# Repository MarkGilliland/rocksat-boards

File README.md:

# rocksat-boards
Mines RockSat-X Circuit Boards. Eagle projects, boards, schematics, and libraries

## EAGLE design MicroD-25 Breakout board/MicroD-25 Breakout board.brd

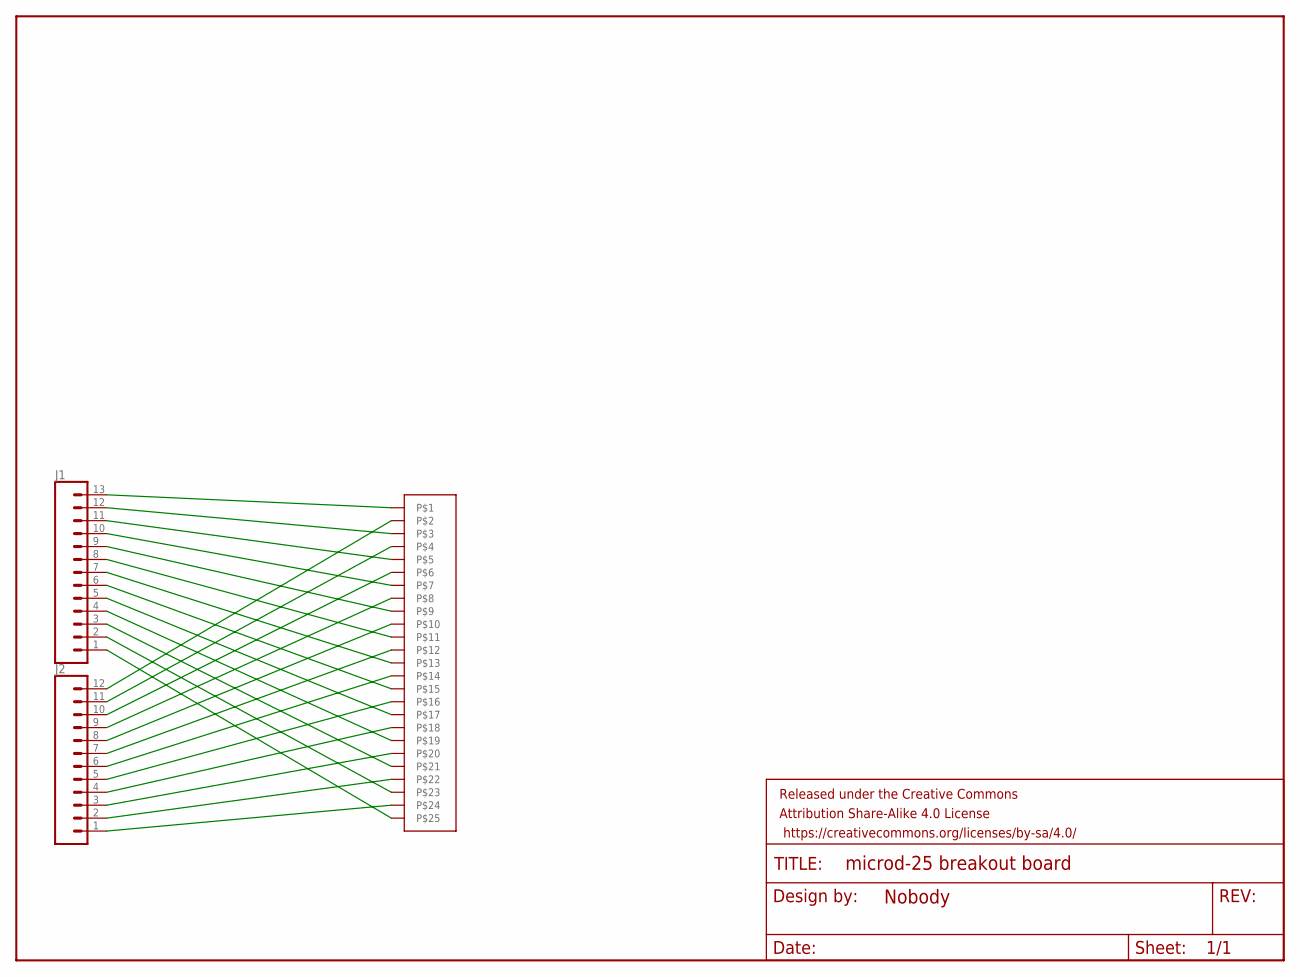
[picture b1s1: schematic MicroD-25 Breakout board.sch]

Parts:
FRAME1: FRAME-LETTERNO_PACKAGE; DUMMY
J1: CONN_13LONGPADS; 1X13-LONGPADS
J2: CONN_12LONGPADS; 1X12_LONGPADS
U$1: MICROD25_FM_RCPT

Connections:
unnamed: J1.13, U$1.PIN1
unnamed: J1.12, U$1.PIN3
unnamed: J1.11, U$1.PIN5
unnamed: J1.10, U$1.PIN7
unnamed: J1.9, U$1.PIN9
unnamed: J1.8, U$1.PIN11
unnamed: J1.7, U$1.PIN13
unnamed: J1.6, U$1.PIN15
unnamed: J1.5, U$1.PIN17
unnamed: J1.4, U$1.PIN19
unnamed: J1.3, U$1.PIN21
unnamed: J1.2, U$1.PIN23
unnamed: J1.1, U$1.PIN25
unnamed: J2.12, U$1.PIN2
unnamed: J2.11, U$1.PIN4
unnamed: J2.10, U$1.PIN6
unnamed: J2.9, U$1.PIN8
unnamed: J2.8, U$1.PIN10
unnamed: J2.7, U$1.PIN12
unnamed: J2.6, U$1.PIN14
unnamed: J2.5, U$1.PIN16
unnamed: J2.4, U$1.PIN18
unnamed: J2.3, U$1.PIN20
unnamed: J2.2, U$1.PIN22
unnamed: J2.1, U$1.PIN24

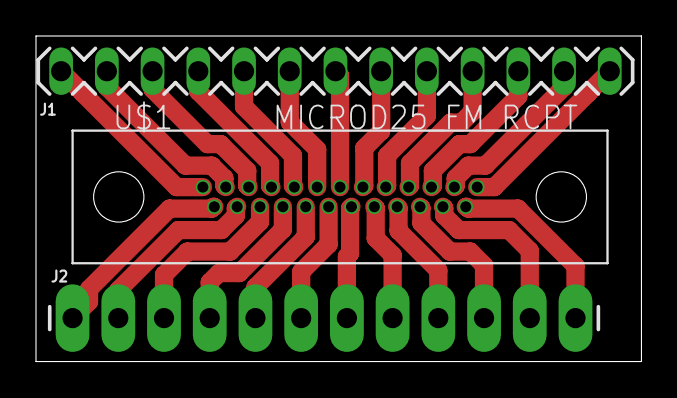
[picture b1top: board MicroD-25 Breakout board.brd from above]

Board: 2 copper layers, 33.6 x 18.1 mm, 4 parts (0 on the bottom side), 25 nets.

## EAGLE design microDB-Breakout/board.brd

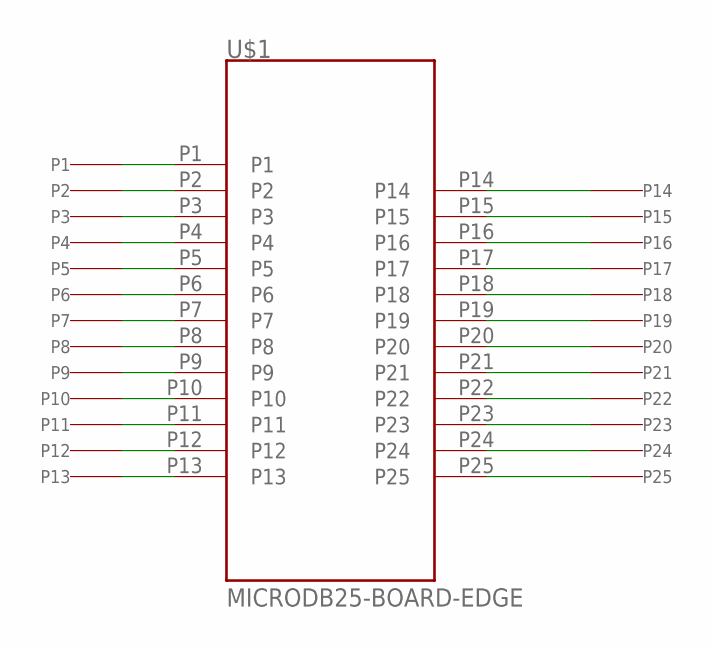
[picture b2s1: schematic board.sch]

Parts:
P1, P2, P3, P4, P5, P6, P7, P8, P9, P10, P11, P12, P13, P14, P15, P16, P17, P18, P19, P20, P21, P22, P23, P24, P25: TP-19MIL
U$1: MICRODB25-BOARD-EDGE

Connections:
unnamed: P1.P1, U$1.P1
unnamed: P2.P1, U$1.P2
unnamed: P3.P1, U$1.P3
unnamed: P4.P1, U$1.P4
unnamed: P5.P1, U$1.P5
unnamed: P6.P1, U$1.P6
unnamed: P7.P1, U$1.P7
unnamed: P8.P1, U$1.P8
unnamed: P9.P1, U$1.P9
unnamed: P10.P1, U$1.P10
unnamed: P11.P1, U$1.P11
unnamed: P12.P1, U$1.P12
unnamed: P13.P1, U$1.P13
unnamed: P14.P1, U$1.P14
unnamed: P15.P1, U$1.P15
unnamed: P16.P1, U$1.P16
unnamed: P17.P1, U$1.P17
unnamed: P18.P1, U$1.P18
unnamed: P19.P1, U$1.P19
unnamed: P20.P1, U$1.P20
unnamed: P21.P1, U$1.P21
unnamed: P22.P1, U$1.P22
unnamed: P23.P1, U$1.P23
unnamed: P24.P1, U$1.P24
unnamed: P25.P1, U$1.P25

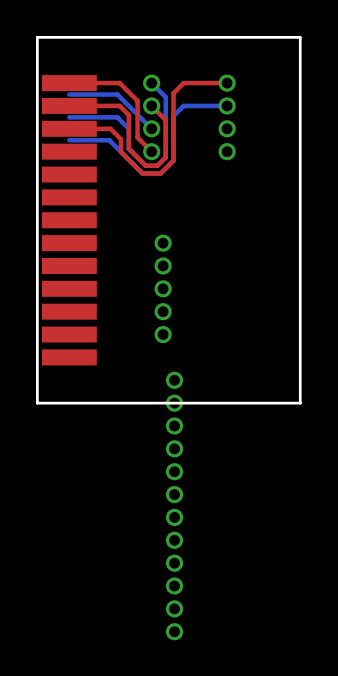
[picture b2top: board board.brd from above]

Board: 2 copper layers, 14.6 x 20.3 mm, 26 parts (0 on the bottom side), 25 nets.

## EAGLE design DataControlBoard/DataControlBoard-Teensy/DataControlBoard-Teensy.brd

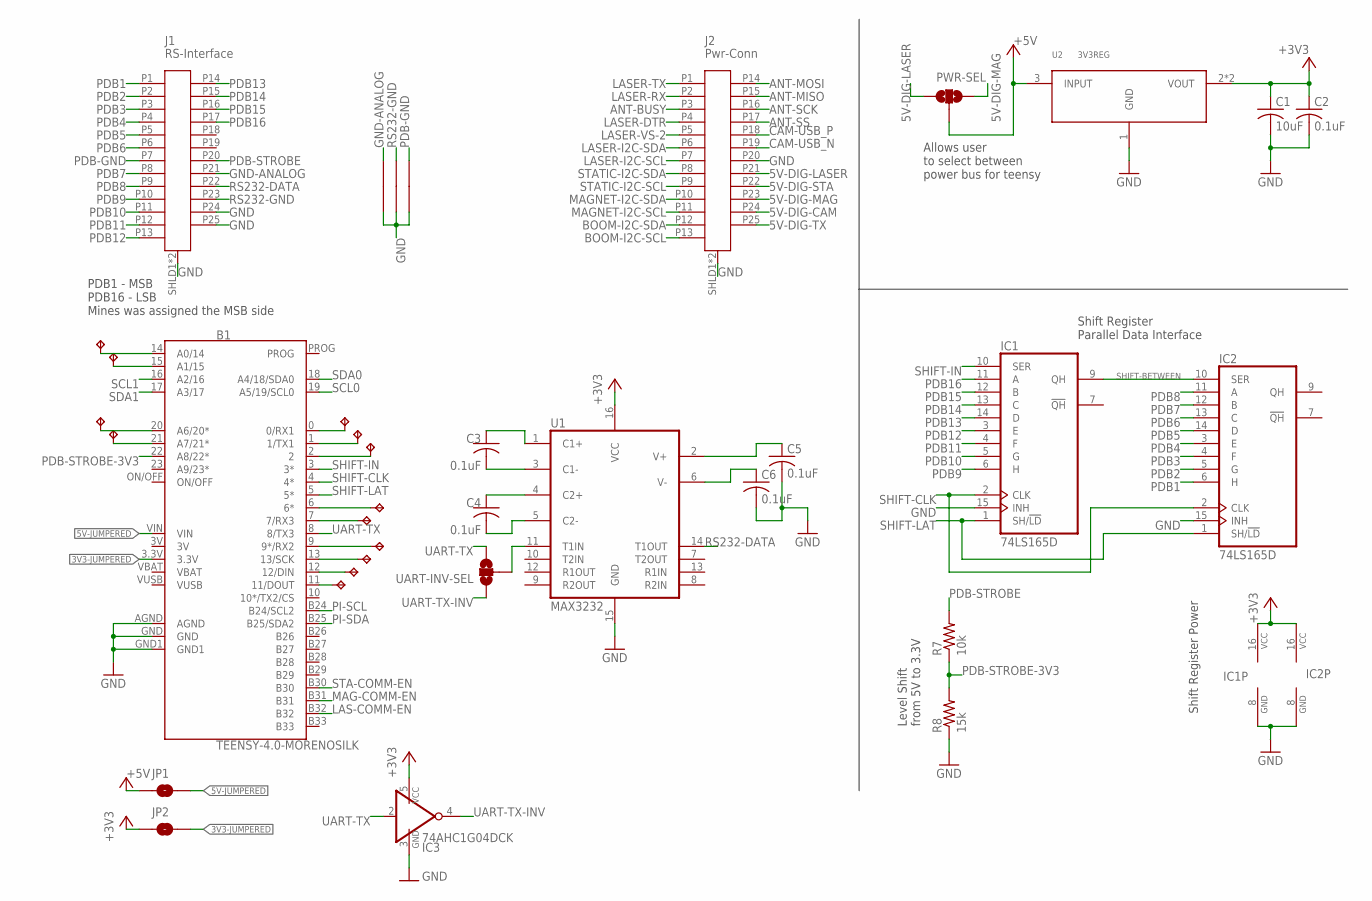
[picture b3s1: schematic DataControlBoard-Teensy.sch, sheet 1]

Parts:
B1: TEENSY-4.0-MORENOSILK; TEENSY-4.0_NOSILK
C1: 10uF; C0805
C2, C3, C4, C5, C6: 0.1uF; C0805
IC1, IC2: 74LS165D; SO16
IC3: 74AHC1G04DCK; SC70-5
J1: RS-Interface; MICRO-D25-RA
J2: Pwr-Conn; MICRO-D25-RA
JP1, JP2: JUMPER-SMT_2_NO_NO-SILK; SMT-JUMPER_2_NO_NO-SILK
PWR-SEL: JUMPER-SMT_3_NO_NO-SILK; SMT-JUMPER_3_NO_NO-SILK
R7: 10k; R0805
R8: 15k; R0805
TP8, TP9, TP10, TP11, TP12, TP13, TP14, TP15, TP16, TP17, TP18, TP19, TP20: TPPAD1-13; P1-13
U1: MAX3232; SO16
U2: 3V3REG; SOT223
U$1, U$2, U$3: GND-MERGER
UART-INV-SEL: JUMPER-SMT_3_NO_NO-SILK; SMT-JUMPER_3_NO_NO-SILK

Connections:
3V: B1.3V
3V3-JUMPERED: B1.3.3V, JP2.2
5V-DIG-CAM: J2.P24; also elsewhere on the board
5V-DIG-LASER: J2.P21, PWR-SEL.1; also elsewhere on the board
5V-DIG-MAG: J2.P23, PWR-SEL.3; also elsewhere on the board
5V-DIG-STA: J2.P22; also elsewhere on the board
5V-DIG-TX: J2.P25; also elsewhere on the board
5V-JUMPERED: B1.VIN, JP1.2
+3V3: C1.1, C2.1, IC1.16 (VCC), IC2.16 (VCC), IC3.5 (VCC), JP2.1, U1.16 (VCC), U2.2 (VOUT), U2.4 (VOUT); also elsewhere on the board
+5V: JP1.1, PWR-SEL.2, U2.3 (INPUT); also elsewhere on the board
ANT-BUSY: J2.P3; also elsewhere on the board
ANT-MISO: J2.P15; also elsewhere on the board
ANT-MOSI: J2.P14; also elsewhere on the board
ANT-SCK: J2.P16; also elsewhere on the board
ANT-SS: J2.P17; also elsewhere on the board
BOOM-I2C-SCL: J2.P13; also elsewhere on the board
BOOM-I2C-SDA: J2.P12; also elsewhere on the board
CAM-USB_N: J2.P19; also elsewhere on the board
CAM-USB_P: J2.P18; also elsewhere on the board
GND: B1.AGND, B1.GND, B1.GND1, C1.2, C2.2, C5.2, C6.2, IC1.8 (GND), IC1.15 (INH), IC2.8 (GND), IC2.15 (INH), IC3.3 (GND), J1.P24, J1.P25, J1.SHLD1 (SHLD), J1.SHLD2 (SHLD), J2.P20, J2.SHLD1 (SHLD), J2.SHLD2 (SHLD), R8.1, U1.15 (GND), U2.1 (GND), U$1.P$1, U$2.P$1, U$3.P$1; also elsewhere on the board
GND-ANALOG: J1.P21, U$1.P$2
LAS-COMM-EN: B1.B32; also elsewhere on the board
LASER-DTR: J2.P4; also elsewhere on the board
LASER-I2C-SCL: J2.P7; also elsewhere on the board
LASER-I2C-SDA: J2.P6; also elsewhere on the board
LASER-RX: J2.P2; also elsewhere on the board
LASER-TX: J2.P1; also elsewhere on the board
LASER-VS-2: J2.P5; also elsewhere on the board
MAG-COMM-EN: B1.B31; also elsewhere on the board
MAGNET-I2C-SCL: J2.P11; also elsewhere on the board
MAGNET-I2C-SDA: J2.P10; also elsewhere on the board
unnamed: B1.0 (0/RX1), TP12.TP
unnamed: B1.1 (1/TX1), TP13.TP
unnamed: B1.2, TP14.TP
unnamed: B1.9 (9*/RX2), TP15.TP
unnamed: B1.13 (13/SCK), TP16.TP
unnamed: B1.12 (12/DIN), TP17.TP
unnamed: B1.11 (11/DOUT), TP18.TP
unnamed: B1.14 (A0/14), TP8.TP
unnamed: B1.15 (A1/15), TP9.TP
unnamed: B1.20 (A6/20*), TP10.TP
unnamed: B1.21 (A7/21*), TP11.TP
unnamed: B1.6 (6*), TP19.TP
unnamed: B1.7 (7/RX3), TP20.TP
unnamed: U1.11 (T1IN), UART-INV-SEL.2
unnamed: C5.1, U1.2 (V+)
unnamed: C6.1, U1.6 (V-)
unnamed: C3.1, U1.1 (C1+)
unnamed: C3.2, U1.3 (C1-)
unnamed: C4.1, U1.4 (C2+)
unnamed: C4.2, U1.5 (C2-)
PDB1: IC2.6 (H), J1.P1
PDB2: IC2.5 (G), J1.P2
PDB3: IC2.4 (F), J1.P3
PDB4: IC2.3 (E), J1.P4
PDB5: IC2.14 (D), J1.P5
PDB6: IC2.13 (C), J1.P6
PDB7: IC2.12 (B), J1.P8
PDB8: IC2.11 (A), J1.P9
PDB9: IC1.6 (H), J1.P10
PDB10: IC1.5 (G), J1.P11
PDB11: IC1.4 (F), J1.P12
PDB12: IC1.3 (E), J1.P13
PDB13: IC1.14 (D), J1.P14
PDB14: IC1.13 (C), J1.P15
PDB15: IC1.12 (B), J1.P16
PDB16: IC1.11 (A), J1.P17
PDB-GND: J1.P7, U$3.P$2
PDB-STROBE: J1.P20, R7.2; also elsewhere on the board
PDB-STROBE-3V3: B1.22 (A8/22*), R7.1, R8.2
PI-SCL: B1.B24 (B24/SCL2); also elsewhere on the board
PI-SDA: B1.B25 (B25/SDA2); also elsewhere on the board
RS232-DATA: J1.P22, U1.14 (T1OUT)
RS232-GND: J1.P23, U$2.P$2
SCL0: B1.19 (A5/19/SCL0); also elsewhere on the board
SCL1: B1.16 (A2/16); also elsewhere on the board
SDA0: B1.18 (A4/18/SDA0); also elsewhere on the board
SDA1: B1.17 (A3/17); also elsewhere on the board
SHIFT-BETWEEN: IC1.9 (QH), IC2.10 (SER)
SHIFT-CLK: B1.4 (4*), IC1.2 (CLK), IC2.2 (CLK)
SHIFT-IN: B1.3 (3*), IC1.10 (SER)
SHIFT-LAT: B1.5 (5*), IC1.1 (SH/!LD), IC2.1 (SH/!LD)
STA-COMM-EN: B1.B30; also elsewhere on the board
STATIC-I2C-SCL: J2.P9; also elsewhere on the board
STATIC-I2C-SDA: J2.P8; also elsewhere on the board
UART-TX: B1.8 (8/TX3), IC3.2 (I), UART-INV-SEL.3
UART-TX-INV: IC3.4 (O), UART-INV-SEL.1
VBAT: B1.VBAT
VUSB: B1.VUSB

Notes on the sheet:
Shift Register Power
Shift Register Parallel Data Interface
Allows user to select between power bus for teensy
Level Shift from 5V to 3.3V
PDB1 - MSB PDB16 - LSB Mines was assigned the MSB side

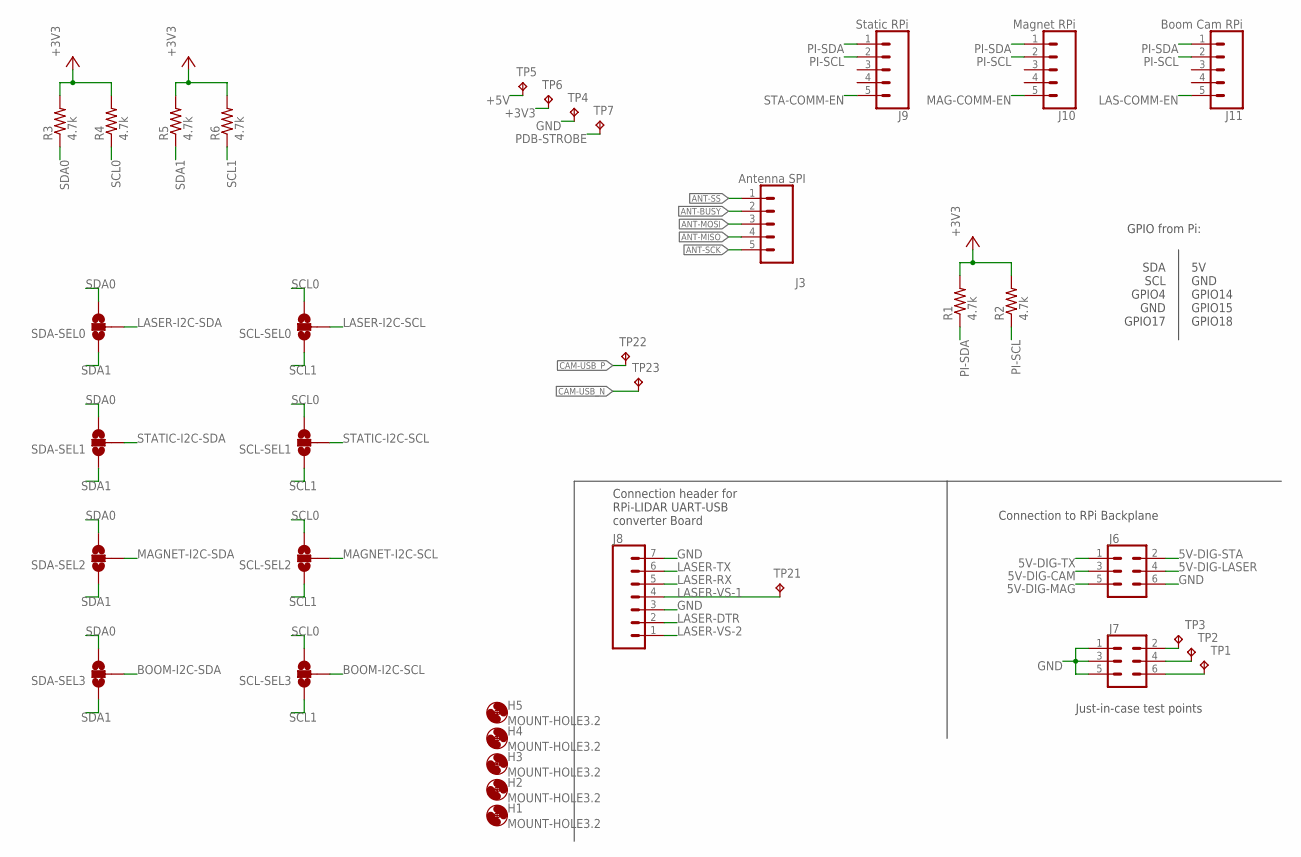
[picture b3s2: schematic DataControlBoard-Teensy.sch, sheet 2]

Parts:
H1, H2, H3, H4, H5: MOUNT-HOLE3.2; 3,2
J3: Antenna SPI; 1X05_LOCK
J6, J7: CONN_03X22X3_SILK_MALE_PTH; 2X3
J8: CONN_07; 1X07
J9: Static RPi; 1X05_LOCK
J10: Magnet RPi; 1X05_LOCK
J11: Boom Cam RPi; 1X05_LOCK
R1, R2, R3, R4, R5, R6: 4.7k; R0805
SCL-SEL0, SCL-SEL1, SCL-SEL2, SCL-SEL3: JUMPER-SMT_3_NO_NO-SILK; SMT-JUMPER_3_NO_NO-SILK
SDA-SEL0, SDA-SEL1, SDA-SEL2, SDA-SEL3: JUMPER-SMT_3_NO_NO-SILK; SMT-JUMPER_3_NO_NO-SILK
TP1, TP2, TP3, TP21, TP22, TP23: TPPAD1-13; P1-13
TP4: GND; P1-13
TP5: 5V; P1-13
TP6: 3.3V; P1-13
TP7: STROBE; P1-13

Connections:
5V-DIG-CAM: J6.3; also elsewhere on the board
5V-DIG-LASER: J6.4; also elsewhere on the board
5V-DIG-MAG: J6.5; also elsewhere on the board
5V-DIG-STA: J6.2; also elsewhere on the board
5V-DIG-TX: J6.1; also elsewhere on the board
+3V3: R1.2, R2.2, R3.2, R4.2, R5.2, R6.2, TP6.TP; also elsewhere on the board
+5V: TP5.TP; also elsewhere on the board
ANT-BUSY: J3.2; also elsewhere on the board
ANT-MISO: J3.4; also elsewhere on the board
ANT-MOSI: J3.3; also elsewhere on the board
ANT-SCK: J3.5; also elsewhere on the board
ANT-SS: J3.1; also elsewhere on the board
BOOM-I2C-SCL: SCL-SEL3.2; also elsewhere on the board
BOOM-I2C-SDA: SDA-SEL3.2; also elsewhere on the board
CAM-USB_N: TP23.TP; also elsewhere on the board
CAM-USB_P: TP22.TP; also elsewhere on the board
GND: J6.6, J7.1, J7.3, J7.5, J8.3, J8.7, TP4.TP; also elsewhere on the board
LAS-COMM-EN: J11.5; also elsewhere on the board
LASER-DTR: J8.2; also elsewhere on the board
LASER-I2C-SCL: SCL-SEL0.2; also elsewhere on the board
LASER-I2C-SDA: SDA-SEL0.2; also elsewhere on the board
LASER-RX: J8.5; also elsewhere on the board
LASER-TX: J8.6; also elsewhere on the board
LASER-VS-1: J8.4, TP21.TP
LASER-VS-2: J8.1; also elsewhere on the board
MAG-COMM-EN: J10.5; also elsewhere on the board
MAGNET-I2C-SCL: SCL-SEL2.2; also elsewhere on the board
MAGNET-I2C-SDA: SDA-SEL2.2; also elsewhere on the board
unnamed: J7.2, TP3.TP
unnamed: J7.4, TP2.TP
unnamed: J7.6, TP1.TP
PDB-STROBE: TP7.TP; also elsewhere on the board
PI-SCL: J9.2, J10.2, J11.2, R2.1; also elsewhere on the board
PI-SDA: J9.1, J10.1, J11.1, R1.1; also elsewhere on the board
SCL0: R4.1, SCL-SEL0.3, SCL-SEL1.3, SCL-SEL2.3, SCL-SEL3.3; also elsewhere on the board
SCL1: R6.1, SCL-SEL0.1, SCL-SEL1.1, SCL-SEL2.1, SCL-SEL3.1; also elsewhere on the board
SDA0: R3.1, SDA-SEL0.3, SDA-SEL1.3, SDA-SEL2.3, SDA-SEL3.3; also elsewhere on the board
SDA1: R5.1, SDA-SEL0.1, SDA-SEL1.1, SDA-SEL2.1, SDA-SEL3.1; also elsewhere on the board
STA-COMM-EN: J9.5; also elsewhere on the board
STATIC-I2C-SCL: SCL-SEL1.2; also elsewhere on the board
STATIC-I2C-SDA: SDA-SEL1.2; also elsewhere on the board

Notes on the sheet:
SDA SCL GPIO4 GND GPIO17
5V GND GPIO14 GPIO15 GPIO18
GPIO from Pi:
Just-in-case test points
Connection to RPi Backplane
Connection header for RPi-LIDAR UART-USB converter Board

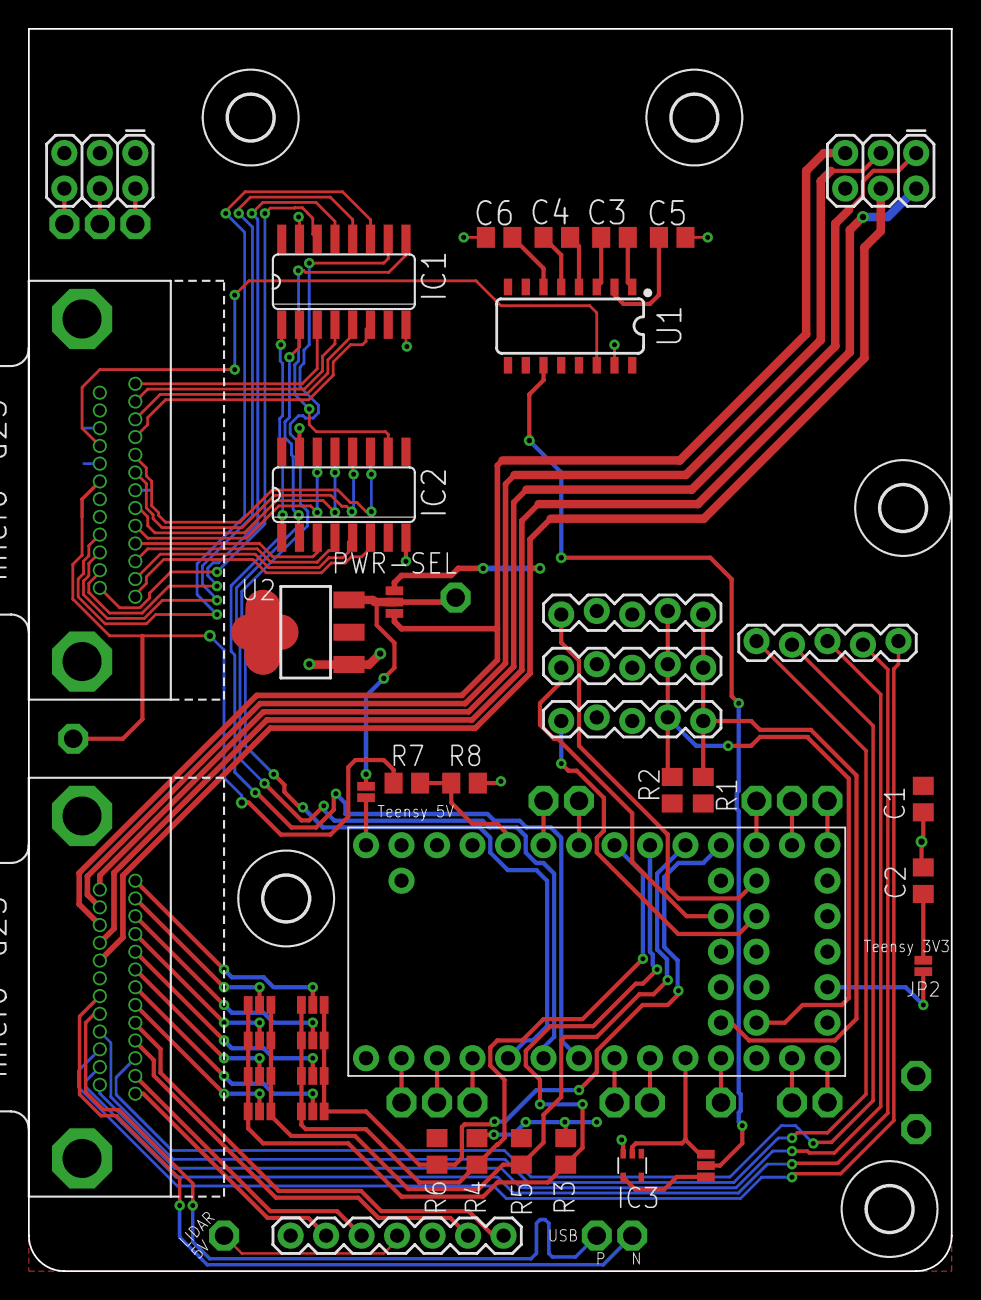
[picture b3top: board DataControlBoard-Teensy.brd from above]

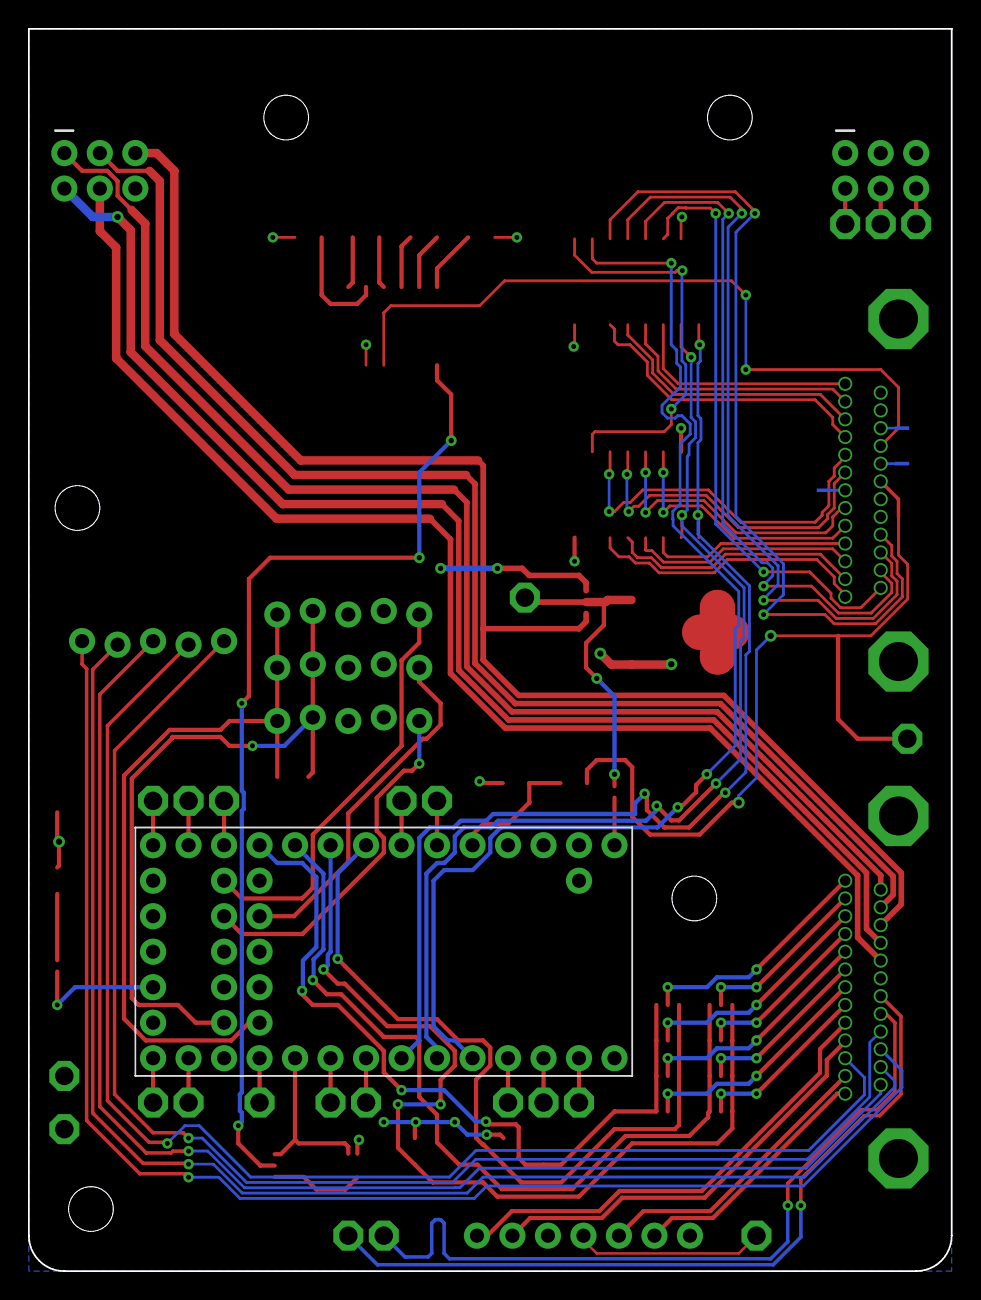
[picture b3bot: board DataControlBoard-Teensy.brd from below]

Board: 2 copper layers, 66.0 x 88.9 mm, 72 parts (3 on the bottom side), 90 nets.

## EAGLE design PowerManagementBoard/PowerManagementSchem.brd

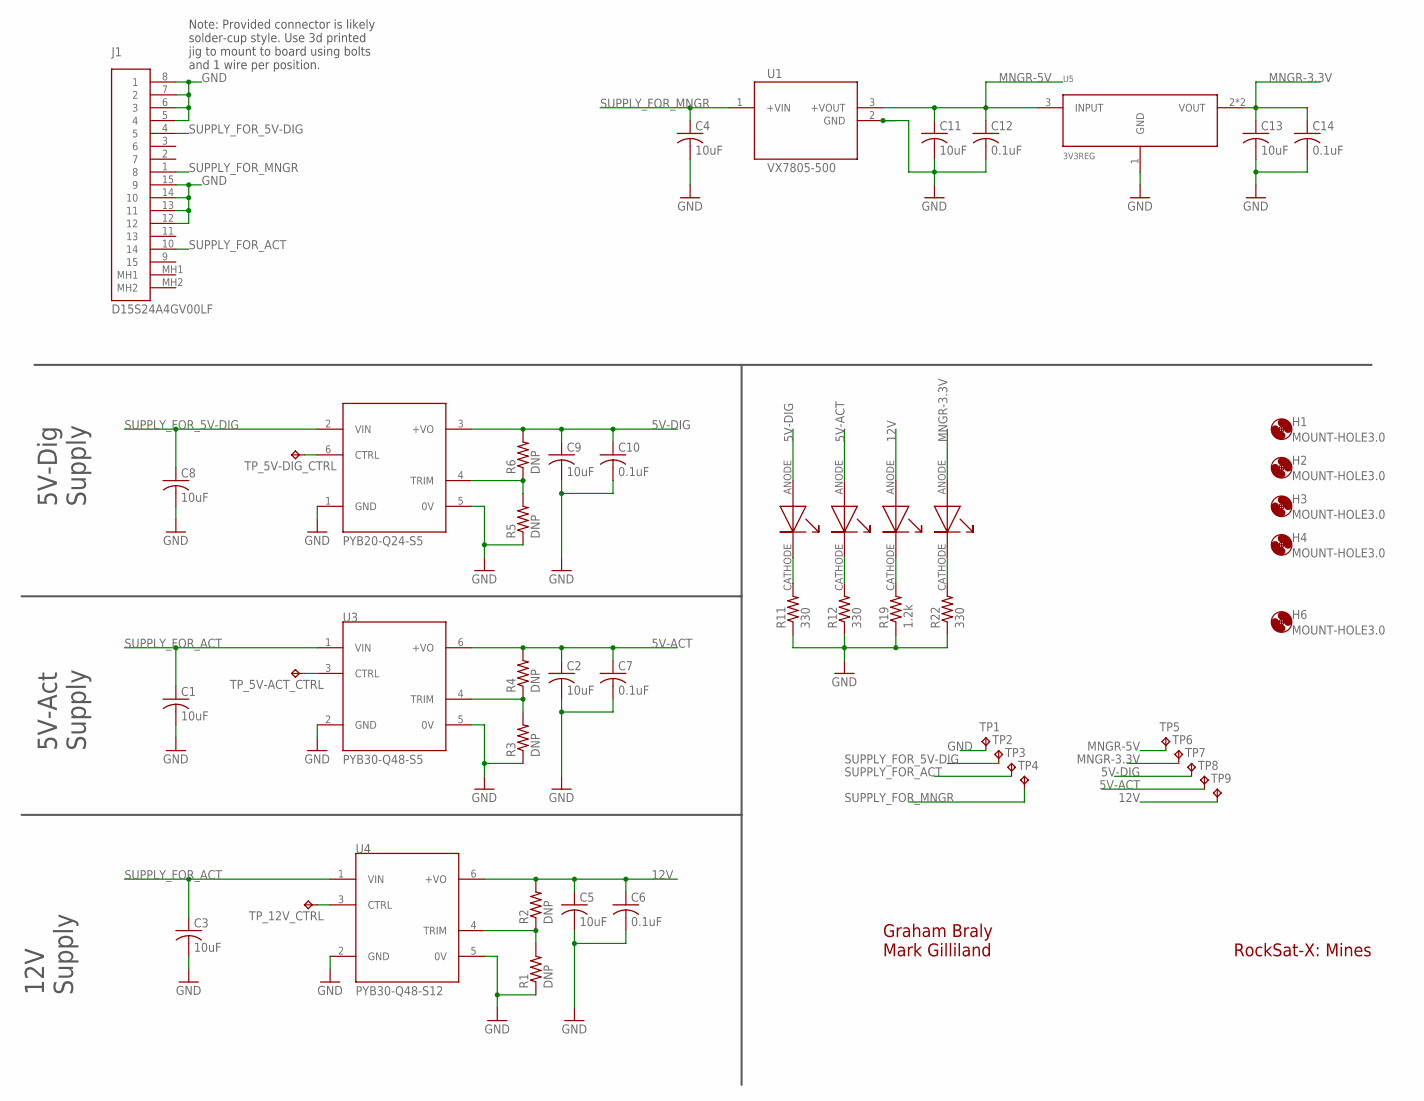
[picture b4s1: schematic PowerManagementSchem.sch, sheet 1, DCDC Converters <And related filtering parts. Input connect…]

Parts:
C1, C3, C4, C8: 10uF; C1206
C2, C5, C9, C11, C13: 10uF; C0805
C6, C7, C10, C12, C14: 0.1uF; C0805
H1, H2, H3, H4, H6: MOUNT-HOLE3.0; 3,0
J1: D15S24A4GV00LF
R1, R2, R3, R4, R5, R6: DNP; R0805
R11, R12, R22: 330; R0805
R19: 1.2k; R0805
TP1, TP2, TP3, TP4, TP5, TP6, TP7, TP8, TP9: TPPAD1-13; P1-13
TP_5V-ACT_CTRL, TP_5V-DIG_CTRL, TP_12V_CTRL: TPPAD1-13; P1-13
U1: VX7805-500; VX78012-500_VX7805-500
U2: PYB20-Q24-S5; CONV_PYB20-Q24-S5
U3: PYB30-Q48-S5; CONV_PYB30-Q48-S5
U4: PYB30-Q48-S12; CONV_PYB30-Q48-S12
U5: 3V3REG; SOT223
U$9, U$10, U$17, U$20: FLAT_LED

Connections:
5V-ACT: C2.1, C7.1, R4.2, TP8.TP, U3.6 (+VO), U$10.ANODE; also elsewhere on the board
5V-ACT-CTRL: TP_5V-ACT_CTRL.TP, U3.3 (CTRL)
5V-ACT-TRIM: R3.2, R4.1, U3.4 (TRIM)
5V-DIG: C9.1, C10.1, R6.2, TP7.TP, U2.3 (+VO), U$9.ANODE; also elsewhere on the board
5V-DIG-CTRL: TP_5V-DIG_CTRL.TP, U2.6 (CTRL)
5V-DIG-TRIM: R5.2, R6.1, U2.4 (TRIM)
12V: C5.1, C6.1, R2.2, TP9.TP, U4.6 (+VO), U$17.ANODE; also elsewhere on the board
12V-CTRL: TP_12V_CTRL.TP, U4.3 (CTRL)
12V-TRIM: R1.2, R2.1, U4.4 (TRIM)
GND: C1.2, C2.2, C3.2, C4.2, C5.2, C6.2, C7.2, C8.2, C9.2, C10.2, C11.2, C12.2, C13.2, C14.2, J1.5 (4), J1.6 (3), J1.7 (2), J1.8 (1), J1.12, J1.13 (11), J1.14 (10), J1.15 (9), R1.1, R11.1, R12.1, R19.1, R22.1, TP1.TP, U1.2 (GND), U2.1 (GND), U3.2 (GND), U4.2 (GND), U4.5 (0V), U5.1 (GND); also elsewhere on the board
MNGR-3.3V: C13.1, C14.1, TP6.TP, U5.2 (VOUT), U5.4 (VOUT), U$20.ANODE; also elsewhere on the board
MNGR-5V: C11.1, C12.1, TP5.TP, U1.3 (+VOUT), U5.3 (INPUT); also elsewhere on the board
unnamed: R3.1, U3.5 (0V)
unnamed: R5.1, U2.5 (0V)
unnamed: R11.2, U$9.CATHODE
unnamed: R12.2, U$10.CATHODE
unnamed: R19.2, U$17.CATHODE
unnamed: R22.2, U$20.CATHODE
SUPPLY_FOR_5V-DIG: C8.1, J1.4 (5), TP2.TP, U2.2 (VIN)
SUPPLY_FOR_ACT: C1.1, C3.1, J1.10 (14), TP3.TP, U3.1 (VIN), U4.1 (VIN)
SUPPLY_FOR_MNGR: C4.1, J1.1 (8), TP4.TP, U1.1 (+VIN)

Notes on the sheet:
Graham Braly Mark Gilliland
RockSat-X: Mines
12V Supply
5V-Act Supply
5V-Dig Supply
Note: Provided connector is likely solder-cup style. Use 3d printed jig to mount to board using bolts and 1 wire per position.

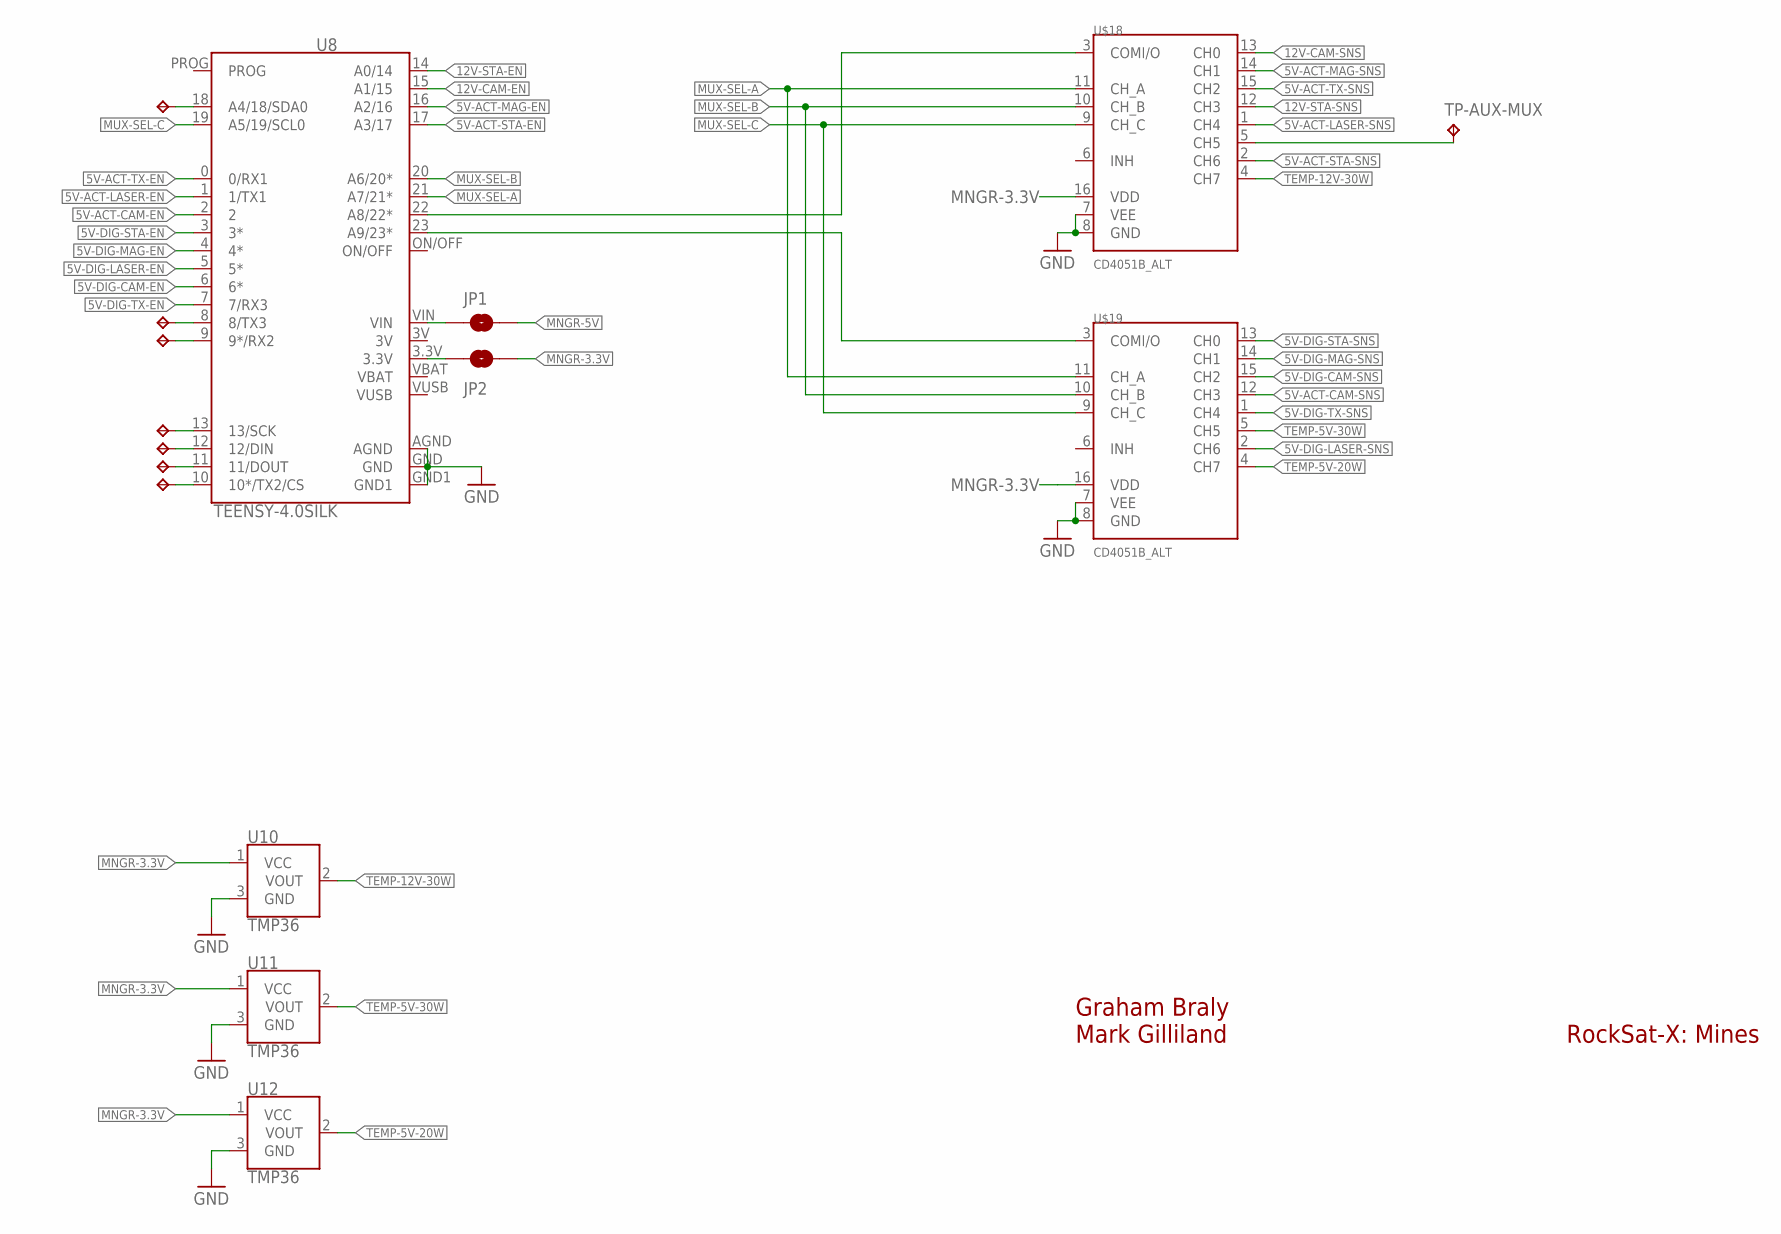
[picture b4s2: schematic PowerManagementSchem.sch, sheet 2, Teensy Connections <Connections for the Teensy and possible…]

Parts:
JP1, JP2: JUMPER-SMT_2_NO_NO-SILK; SMT-JUMPER_2_NO_NO-SILK
TP10, TP11, TP12, TP13, TP14, TP15, TP16: TPPAD1-13; P1-13
TP-AUX-MUX: TPPAD1-13; P1-13
U8: TEENSY-4.0SILK; TEENSY-4.0
U10, U11, U12: TMP36; TO-92
U$18, U$19: CD4051B_ALT; SOIC16N

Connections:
3V: U8.3V
5V-ACT-CAM-EN: U8.2; also elsewhere on the board
5V-ACT-CAM-SNS: U$19.12 (CH3); also elsewhere on the board
5V-ACT-LASER-EN: U8.1 (1/TX1); also elsewhere on the board
5V-ACT-LASER-SNS: U$18.1 (CH4); also elsewhere on the board
5V-ACT-MAG-EN: U8.16 (A2/16); also elsewhere on the board
5V-ACT-MAG-SNS: U$18.14 (CH1); also elsewhere on the board
5V-ACT-STA-EN: U8.17 (A3/17); also elsewhere on the board
5V-ACT-STA-SNS: U$18.2 (CH6); also elsewhere on the board
5V-ACT-TX-EN: U8.0 (0/RX1); also elsewhere on the board
5V-ACT-TX-SNS: U$18.15 (CH2); also elsewhere on the board
5V-DIG-CAM-EN: U8.6 (6*); also elsewhere on the board
5V-DIG-CAM-SNS: U$19.15 (CH2); also elsewhere on the board
5V-DIG-LASER-EN: U8.5 (5*); also elsewhere on the board
5V-DIG-LASER-SNS: U$19.2 (CH6); also elsewhere on the board
5V-DIG-MAG-EN: U8.4 (4*); also elsewhere on the board
5V-DIG-MAG-SNS: U$19.14 (CH1); also elsewhere on the board
5V-DIG-STA-EN: U8.3 (3*); also elsewhere on the board
5V-DIG-STA-SNS: U$19.13 (CH0); also elsewhere on the board
5V-DIG-TX-EN: U8.7 (7/RX3); also elsewhere on the board
5V-DIG-TX-SNS: U$19.1 (CH4); also elsewhere on the board
12V-CAM-EN: U8.15 (A1/15); also elsewhere on the board
12V-CAM-SNS: U$18.13 (CH0); also elsewhere on the board
12V-STA-EN: U8.14 (A0/14); also elsewhere on the board
12V-STA-SNS: U$18.12 (CH3); also elsewhere on the board
CURRENT-SNS-A: U8.22 (A8/22*), U$18.3 (COMI/O)
CURRENT-SNS-B: U8.23 (A9/23*), U$19.3 (COMI/O)
GND: U8.AGND, U8.GND, U8.GND1, U10.3 (GND), U11.3 (GND), U12.3 (GND), U$18.7 (VEE), U$18.8 (GND), U$19.7 (VEE), U$19.8 (GND); also elsewhere on the board
MNGR-3.3V: JP2.2, U10.1 (VCC), U11.1 (VCC), U12.1 (VCC), U$18.16 (VDD), U$19.16 (VDD); also elsewhere on the board
MNGR-5V: JP1.2; also elsewhere on the board
MUX-SEL-A: U8.21 (A7/21*), U$18.11 (CH_A), U$19.11 (CH_A)
MUX-SEL-B: U8.20 (A6/20*), U$18.10 (CH_B), U$19.10 (CH_B)
MUX-SEL-C: U8.19 (A5/19/SCL0), U$18.9 (CH_C), U$19.9 (CH_C)
unnamed: TP-AUX-MUX.TP, U$18.5 (CH5)
unnamed: TP10.TP, U8.8 (8/TX3)
unnamed: TP11.TP, U8.9 (9*/RX2)
unnamed: TP12.TP, U8.13 (13/SCK)
unnamed: TP13.TP, U8.12 (12/DIN)
unnamed: TP14.TP, U8.11 (11/DOUT)
unnamed: TP15.TP, U8.10 (10*/TX2/CS)
unnamed: TP16.TP, U8.18 (A4/18/SDA0)
unnamed: JP1.1, U8.VIN
unnamed: JP2.1, U8.3.3V
TEMP-5V-20W: U12.2 (VOUT), U$19.4 (CH7)
TEMP-5V-30W: U11.2 (VOUT), U$19.5 (CH5)
TEMP-12V-30W: U10.2 (VOUT), U$18.4 (CH7)
VBAT: U8.VBAT
VUSB: U8.VUSB

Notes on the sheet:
Graham Braly Mark Gilliland
RockSat-X: Mines

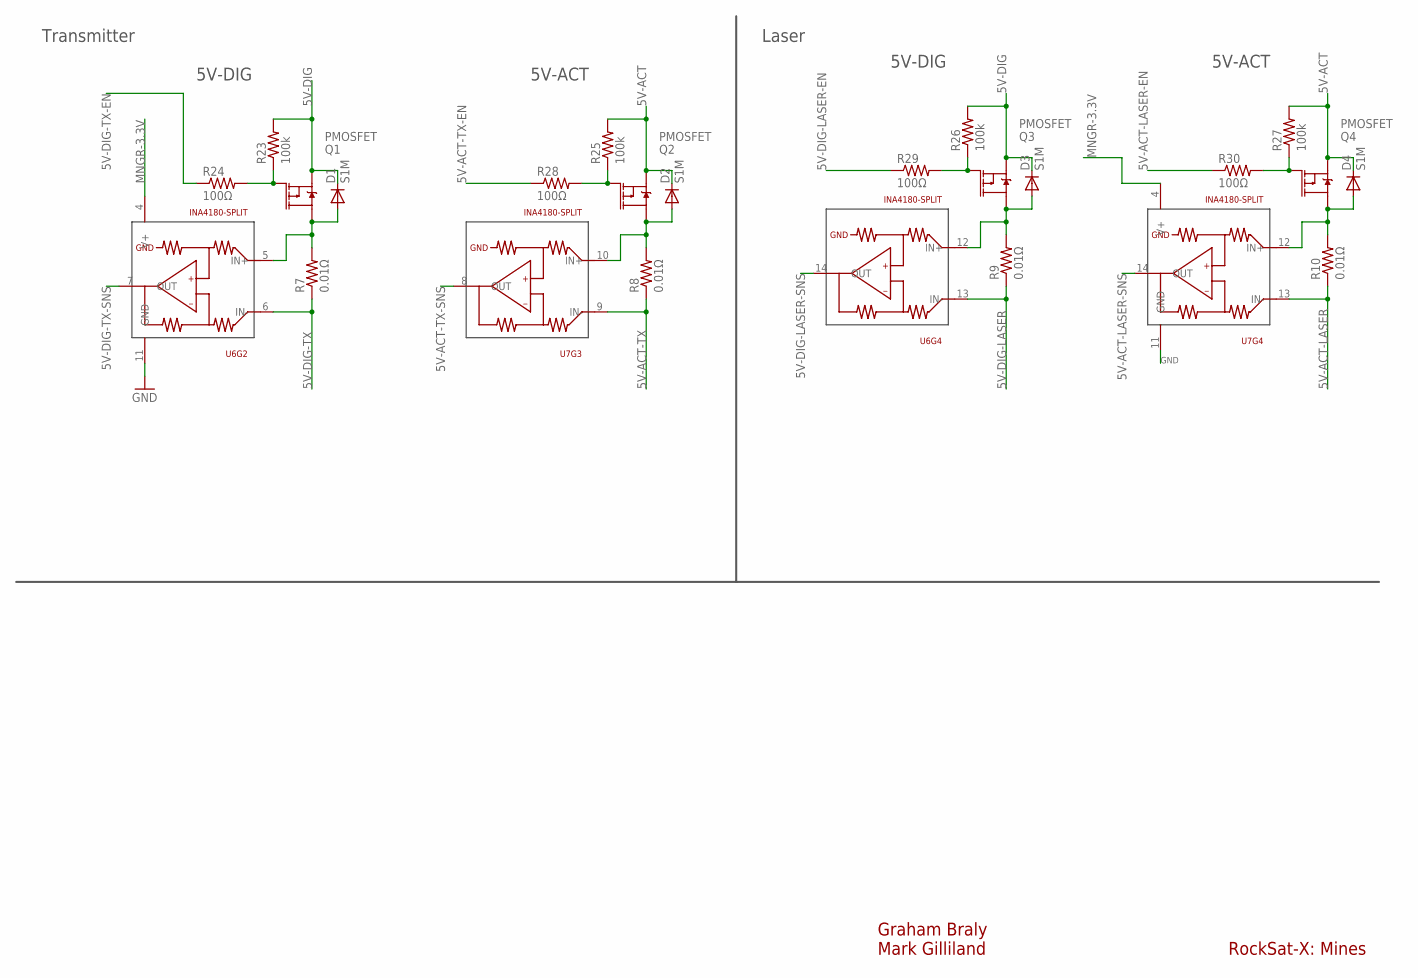
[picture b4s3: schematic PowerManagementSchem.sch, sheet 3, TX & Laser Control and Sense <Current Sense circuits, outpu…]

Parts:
D1, D2, D3, D4: S1M; SMA
Q1, Q2, Q3, Q4: PMOSFET; DPAK
R7, R8, R9, R10: 0.01Ω; R1206
R23, R25, R26, R27: 100k; R0805
R24, R28, R29, R30: 100Ω; R0805
U6, U7: INA4180-SPLIT; TSSOP14

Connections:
5V-ACT: D2.C, D4.C, Q2.3 (S), Q4.3 (S), R25.2, R27.2; also elsewhere on the board
5V-ACT-LASER: R10.1, U7.13 (IN-); also elsewhere on the board
5V-ACT-LASER-EN: R30.1; also elsewhere on the board
5V-ACT-LASER-SNS: U7.14 (OUT); also elsewhere on the board
5V-ACT-TX: R8.1, U7.9 (IN-); also elsewhere on the board
5V-ACT-TX-EN: R28.1; also elsewhere on the board
5V-ACT-TX-SNS: U7.8 (OUT); also elsewhere on the board
5V-DIG: D1.C, D3.C, Q1.3 (S), Q3.3 (S), R23.2, R26.2; also elsewhere on the board
5V-DIG-LASER: R9.1, U6.13 (IN-); also elsewhere on the board
5V-DIG-LASER-EN: R29.1; also elsewhere on the board
5V-DIG-LASER-SNS: U6.14 (OUT); also elsewhere on the board
5V-DIG-TX: R7.1, U6.6 (IN-); also elsewhere on the board
5V-DIG-TX-EN: R24.1; also elsewhere on the board
5V-DIG-TX-SNS: U6.7 (OUT); also elsewhere on the board
GND: U6.11 (GND), U7.11 (GND); also elsewhere on the board
MNGR-3.3V: U6.4 (V+), U7.4 (V+); also elsewhere on the board
unnamed: Q1.1 (G), R23.1, R24.2
unnamed: Q2.1 (G), R25.1, R28.2
unnamed: D1.A, Q1.4 (D), R7.2, U6.5 (IN+)
unnamed: D2.A, Q2.4 (D), R8.2, U7.10 (IN+)
unnamed: Q3.1 (G), R26.1, R29.2
unnamed: D3.A, Q3.4 (D), R9.2, U6.12 (IN+)
unnamed: Q4.1 (G), R27.1, R30.2
unnamed: D4.A, Q4.4 (D), R10.2, U7.12 (IN+)

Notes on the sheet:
Graham Braly Mark Gilliland
RockSat-X: Mines
Transmitter
5V-DIG
5V-ACT
Laser

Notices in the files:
parts and their libraries:
SparkFun-IC-Microcontroller: Licensing: Creative Commons ShareAlike 4.0 International - https://creativecommons.org/licenses/by-sa/4.0
SparkFun-Aesthetics: Released under the Creative Commons Attribution Share-Alike 4.0 License
SparkFun-Aesthetics: https://creativecommons.org/licenses/by-sa/4.0
